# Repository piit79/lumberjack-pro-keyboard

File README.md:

# Lumberjack Pro - Hotswap ortholinear 60% keyboard PCB based on the Frood/nice!nano

Lumberjack is a hotswap split 5x12 ortholinear keyboard PCB based on the Frood or nice!nano controllers, and using mostly through-hole components.

The goal of this project is to build a hotswap ortholinear PCB that fits in many standard 60% tray mount cases.

Inspired by the [Plaid keyboard](https://github.com/hsgw/plaid).

* Designed to be easy to build with minimal soldering experience
* Uses either the modern [Frood](https://42keebs.eu/shop/parts/controllers/frood-rp2040-pro-micro-controller/) (wired) or [nice!nano](https://nicekeyboards.com/nice-nano) (wireless) controllers instead of the old-school 8bit ATmega MCU
* Uses Kailh hotswap sockets for easy switch swaps
* Get that visible component aesthetic in a standard 60% tray-mount case
* Supports both USB Mini and USB-C
* Plateless or with FR4 switch plates

# Kit availability

Complete kits can be purchased at [42. Keebs](https://42keebs.eu/shop/kits/pro-micro-based/lumberjack-pro-hotswap-50-ortho-kit/)

# Ordering parts

See the [Bill of materials](BOM.md) for a detailed list of the required parts.

PCBs can be manufactuered by a variety of online PCB fabricators. You can use [PCBShopper](https://pcbshopper.com/) to search for the best price.

The [zip file in the releases](https://github.com/piit79/lumberjack-pro-keyboard/releases) contains the gerber files your fabricator will need to make the PCB.

When uploading the gerber zip files, use the default PCB settings.

Note that when uploading to JLCPCB, the upload tool may not detect the dimensions of the PCB from the gerber files and may not generate a preview image. This appears to be an issue with JLCPCB and you can manually enter the PCB size as 94.6x285mm.

If you want to use a plate, there are gerbers for an FR4 plate. You will need two plates, one for each half of the keyboard.

# Construction

Solder all the components onto the top side of the PCB except the USB connector which should be on the back of the board. Leave the larger components until last so that the board will lie flat upsidedown while you solder the resistors and capacitors.

Ensure that the diodes are installed in the correct orientation. The square pad is for the side with the black stripe.

See [the build guide](guide.md) for more information.

## Need help?

Have questions or need help, reach out via the [42. Keebs Discord server](https://42keebs.eu/discord) where you will find many helpful Lumberjack owners.

# Firmware

Firmware is available in our [QMK/Vial fork](https://github.com/piit79/vial-qmk/tree/vial/keyboards/42keebs/lumberjack_pro).

Follow the [QMK firmware instructions](https://docs.qmk.fm/#/flashing) to build and flash the firmware.

To put the controller into bootloader mode so it is ready to recieve firmware, do the following:

* A brand new Frood and nice!nano will enter bootloader mode automatically
* On the Frood, hold the BOOT button while pressing the RESET button
* If the Frood is flashed with a QMK/Vial firmware, double-press the RESET button quickly
* On the nice!nano, double-press the RESET button quickly

Once the controller enters the bootloader mode, it will present itself as a USB mass storage device ("USB flash drive"). To flash the firmware .uf2 file, simply copy it to the drive.

# Component cover

Cut a piece of 2mm thick acrylic to size (95x57mm) and drill 4 m2 holes in the corners for the standoffs. Use the PCB or cover.dxf as a guide for the hole positions, you can also use cover.dxf for laser cutting the correct size acrylic.

Affix the 4 standoffs to the PCB with screws from underneath the PCB. Use the remaining 4 screws to attach the acrylic to the top of the standoffs.

# Revisions

## Rev1

* Initial revision using hotswap sockets with support for both Frood and nice!nano controllers

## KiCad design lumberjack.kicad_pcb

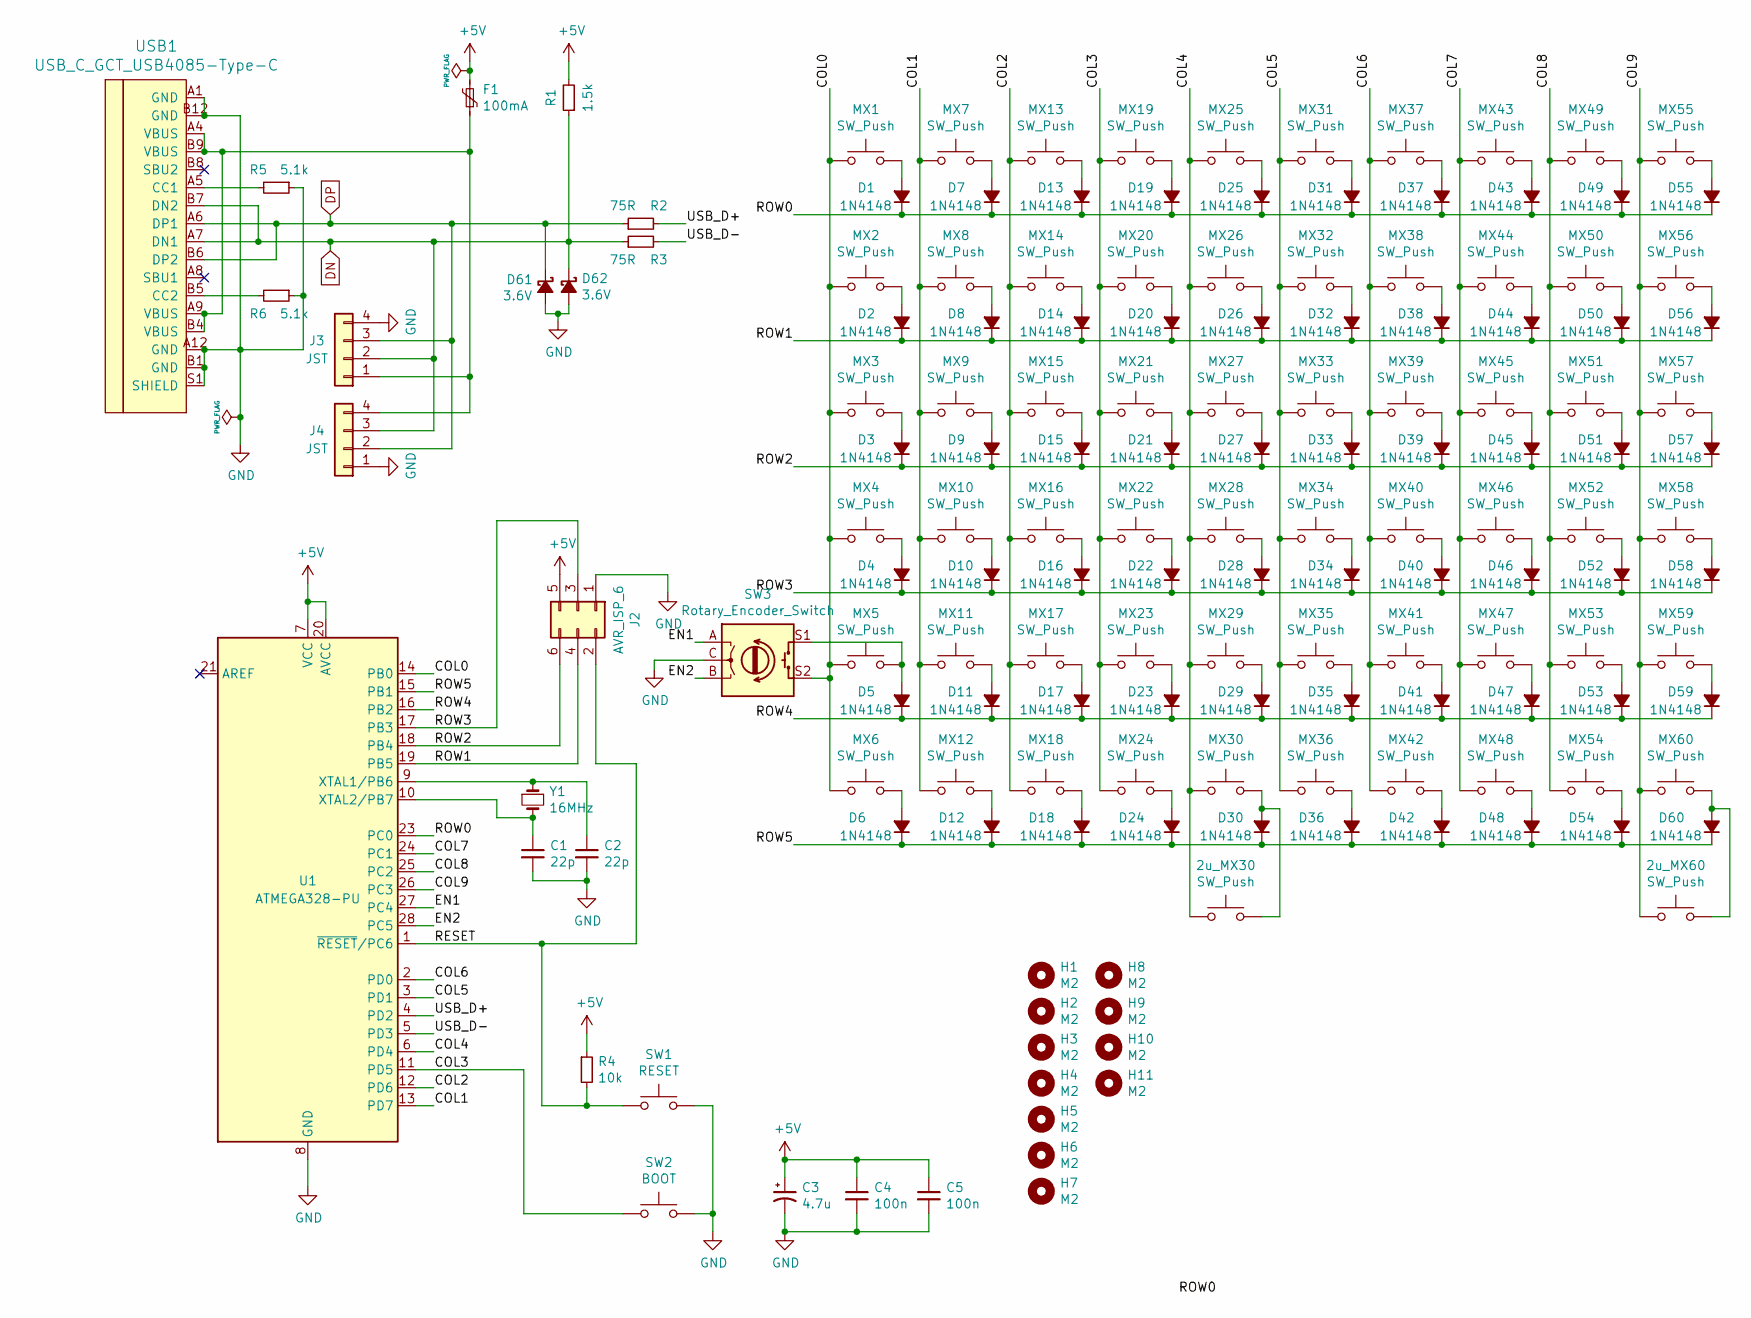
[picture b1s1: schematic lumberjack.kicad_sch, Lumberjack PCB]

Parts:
2u_MX30, 2u_MX60: SW_Push; MX_PCB_200B
C1, C2: 22p; C_Disc_D3.0mm_W1.6mm_P2.50mm
C3: 4.7u; CP_Radial_D4.0mm_P1.50mm
C4, C5: 100n; C_Disc_D4.3mm_W1.9mm_P5.00mm
D1, D2, D3, D4, D5, D6, D7, D8, D9, D10, D11, D12, D13, D14, D15, D16, D17, D18, D19, D20, D21, D22, D23, D24, D25, D26, D27, D28, D29, D30, D31, D32, D33, D34, D35, D36, D37, D38, D39, D40, D41, D42, D43, D44, D45, D46, D47, D48, D49, D50, D51, D52, D53, D54, D55, D56, D57, D58, D59, D60: 1N4148; D_DO-35_SOD27_P7.62mm_Horizontal
D61, D62: 3.6V; D_DO-35_SOD27_P7.62mm_Horizontal
F1: 100mA; Fuse_Bourns_MF-RHT100
H1, H2, H3, H4: M2; MountingHole_M2
H5, H6, H7: M2; MountingSlot_M2
H8, H9, H10, H11: M2; MountingHole_2.2mm_M2
J2: AVR_ISP_6; PinHeader_2x03_P2.54mm_Vertical
J3: JST; JST_SH_SM04B-SRSS-TB_1x04-1MP_P1.00mm_Horizontal
J4: JST; S4B-ZRLFSN
MX1, MX2, MX3, MX4, MX5, MX6, MX7, MX9, MX10, MX11, MX12, MX13, MX14, MX15, MX16, MX17, MX18, MX19, MX20, MX21, MX22, MX23, MX24, MX25, MX26, MX27, MX28, MX29, MX30, MX31, MX32, MX33, MX34, MX35, MX36, MX37, MX38, MX39, MX40, MX41, MX42, MX43, MX44, MX45, MX46, MX47, MX48, MX49, MX50, MX51, MX52, MX53, MX54, MX55, MX56, MX57, MX58, MX59, MX60: SW_Push; MX
MX8: SW_Push; MX_NTHSTH
R1: 1.5k; R_Axial_DIN0204_L3.6mm_D1.6mm_P7.62mm_Horizontal
R2, R3: 75R; R_Axial_DIN0204_L3.6mm_D1.6mm_P7.62mm_Horizontal
R4: 10k; R_Axial_DIN0204_L3.6mm_D1.6mm_P7.62mm_Horizontal
R5, R6: 5.1k; R_Axial_DIN0204_L3.6mm_D1.6mm_P7.62mm_Horizontal
SW1: RESET; SW_PUSH_6mm
SW2: BOOT; SW_PUSH_6mm
SW3: Rotary_Encoder_Switch; RotaryEncoder_Alps_EC11E-Switch_Vertical_H20mm-for-MX
U1: ATMEGA328-PU; DIP-28_W7.62mm
USB1: USB_C_GCT_USB4085-Type-C; USB_C_GCT_USB4085-offset-pads
Y1: 16MHz; Crystal_HC49-4H_Vertical

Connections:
+5V: C3.1, C4.1, C5.1, F1.2, J2.5, R1.2, R4.1, U1.7 (VCC), U1.20 (AVCC)
/COL0: MX1.2, MX2.2, MX3.2, MX4.2, MX5.2, MX6.2, SW3.S2, U1.14 (PB0)
/COL1: MX7.2, MX8.2, MX9.2, MX10.2, MX11.2, MX12.2, U1.13 (PD7)
/COL2: MX13.2, MX14.2, MX15.2, MX16.2, MX17.2, MX18.2, U1.12 (PD6)
/COL3: MX19.2, MX20.2, MX21.2, MX22.2, MX23.2, MX24.2, SW2.1, U1.11 (PD5)
/COL4: 2u_MX30.2, MX25.2, MX26.2, MX27.2, MX28.2, MX29.2, MX30.2, U1.6 (PD4)
/COL5: MX31.2, MX32.2, MX33.2, MX34.2, MX35.2, MX36.2, U1.3 (PD1)
/COL6: MX37.2, MX38.2, MX39.2, MX40.2, MX41.2, MX42.2, U1.2 (PD0)
/COL7: MX43.2, MX44.2, MX45.2, MX46.2, MX47.2, MX48.2, U1.24 (PC1)
/COL8: MX49.2, MX50.2, MX51.2, MX52.2, MX53.2, MX54.2, U1.25 (PC2)
/COL9: 2u_MX60.2, MX55.2, MX56.2, MX57.2, MX58.2, MX59.2, MX60.2, U1.26 (PC3)
/LED1: SW3.B, U1.28 (PC5); also elsewhere on the board
/LED2: SW3.A, U1.27 (PC4); also elsewhere on the board
/RESET: J2.2, R4.2, SW1.1, U1.1 (~RESET/PC6)
/ROW0: D1.1 (K), D7.1 (K), D13.1 (K), D19.1 (K), D25.1 (K), D31.1 (K), D37.1 (K), D43.1 (K), D49.1 (K), D55.1 (K), U1.23 (PC0)
/ROW1: D2.1 (K), D8.1 (K), D14.1 (K), D20.1 (K), D26.1 (K), D32.1 (K), D38.1 (K), D44.1 (K), D50.1 (K), D56.1 (K), J2.4, U1.19 (PB5)
/ROW2: D3.1 (K), D9.1 (K), D15.1 (K), D21.1 (K), D27.1 (K), D33.1 (K), D39.1 (K), D45.1 (K), D51.1 (K), D57.1 (K), J2.6, U1.18 (PB4)
/ROW3: D4.1 (K), D10.1 (K), D16.1 (K), D22.1 (K), D28.1 (K), D34.1 (K), D40.1 (K), D46.1 (K), D52.1 (K), D58.1 (K), J2.3, U1.17 (PB3)
/ROW4: D5.1 (K), D11.1 (K), D17.1 (K), D23.1 (K), D29.1 (K), D35.1 (K), D41.1 (K), D47.1 (K), D53.1 (K), D59.1 (K), U1.16 (PB2)
/ROW5: D6.1 (K), D12.1 (K), D18.1 (K), D24.1 (K), D30.1 (K), D36.1 (K), D42.1 (K), D48.1 (K), D54.1 (K), D60.1 (K), U1.15 (PB1)
/USB_D+: R2.2, U1.4 (PD2)
/USB_D-: R3.2, U1.5 (PD3)
GND: C1.2, C2.2, C3.2, C4.2, C5.2, D61.2 (A), D62.2 (A), J2.1, J3.4, J4.1, R5.1, R6.1, SW1.2, SW2.2, SW3.C, U1.8 (GND), U1.22 (GND), USB1.A1 (GND), USB1.A12 (GND), USB1.B1 (GND), USB1.B12 (GND), USB1.S1 (SHIELD); also elsewhere on the board
unnamed: 2u_MX30.1, D30.2 (A), MX30.1
unnamed: 2u_MX60.1, D60.2 (A), MX60.1
unnamed: C1.1, U1.10 (XTAL2/PB7), Y1.2
unnamed: C2.1, U1.9 (XTAL1/PB6), Y1.1
unnamed: D1.2 (A), MX1.1
unnamed: D2.2 (A), MX2.1
unnamed: D3.2 (A), MX3.1
unnamed: D4.2 (A), MX4.1
unnamed: D5.2 (A), MX5.1, SW3.S1
unnamed: D6.2 (A), MX6.1
unnamed: D7.2 (A), MX7.1
unnamed: D8.2 (A), MX8.1
unnamed: D9.2 (A), MX9.1
unnamed: D10.2 (A), MX10.1
unnamed: D11.2 (A), MX11.1
unnamed: D12.2 (A), MX12.1
unnamed: D13.2 (A), MX13.1
unnamed: D14.2 (A), MX14.1
unnamed: D15.2 (A), MX15.1
unnamed: D16.2 (A), MX16.1
unnamed: D17.2 (A), MX17.1
unnamed: D18.2 (A), MX18.1
unnamed: D19.2 (A), MX19.1
unnamed: D20.2 (A), MX20.1
unnamed: D21.2 (A), MX21.1
unnamed: D22.2 (A), MX22.1
unnamed: D23.2 (A), MX23.1
unnamed: D24.2 (A), MX24.1
unnamed: D25.2 (A), MX25.1
unnamed: D26.2 (A), MX26.1
unnamed: D27.2 (A), MX27.1
unnamed: D28.2 (A), MX28.1
unnamed: D29.2 (A), MX29.1
unnamed: D31.2 (A), MX31.1
unnamed: D32.2 (A), MX32.1
unnamed: D33.2 (A), MX33.1
unnamed: D34.2 (A), MX34.1
unnamed: D35.2 (A), MX35.1
unnamed: D36.2 (A), MX36.1
unnamed: D37.2 (A), MX37.1
unnamed: D38.2 (A), MX38.1
unnamed: D39.2 (A), MX39.1
unnamed: D40.2 (A), MX40.1
unnamed: D41.2 (A), MX41.1
unnamed: D42.2 (A), MX42.1
unnamed: D43.2 (A), MX43.1
unnamed: D44.2 (A), MX44.1
unnamed: D45.2 (A), MX45.1
unnamed: D46.2 (A), MX46.1
unnamed: D47.2 (A), MX47.1
unnamed: D48.2 (A), MX48.1
unnamed: D49.2 (A), MX49.1
unnamed: D50.2 (A), MX50.1
unnamed: D51.2 (A), MX51.1
unnamed: D52.2 (A), MX52.1
unnamed: D53.2 (A), MX53.1
unnamed: D54.2 (A), MX54.1
unnamed: D55.2 (A), MX55.1
unnamed: D56.2 (A), MX56.1
unnamed: D57.2 (A), MX57.1
unnamed: D58.2 (A), MX58.1
unnamed: D59.2 (A), MX59.1
unnamed: F1.1, J3.1, J4.4, USB1.A4 (VBUS), USB1.A9 (VBUS), USB1.B4 (VBUS), USB1.B9 (VBUS)
unnamed: R5.2, USB1.A5 (CC1)
unnamed: R6.2, USB1.B5 (CC2)

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
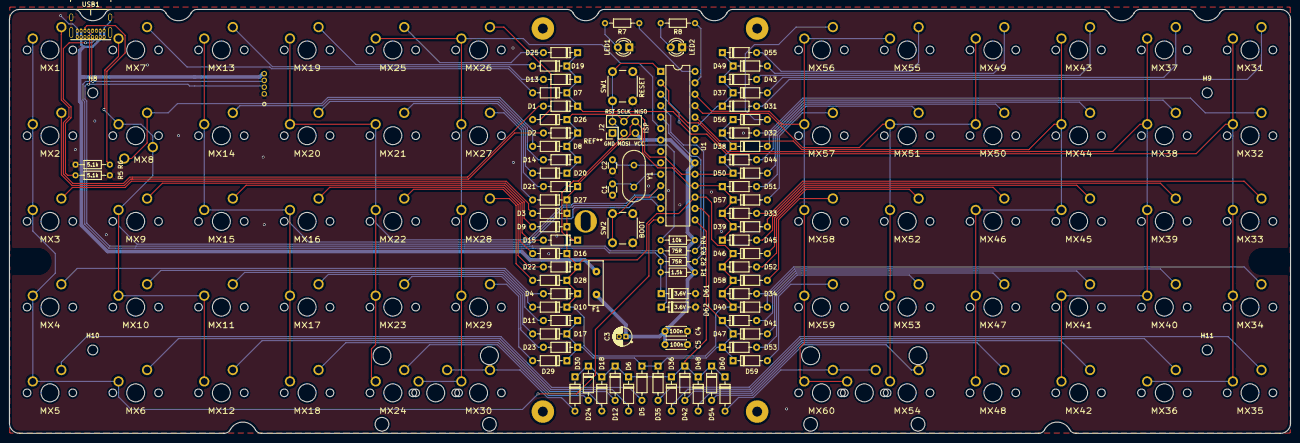
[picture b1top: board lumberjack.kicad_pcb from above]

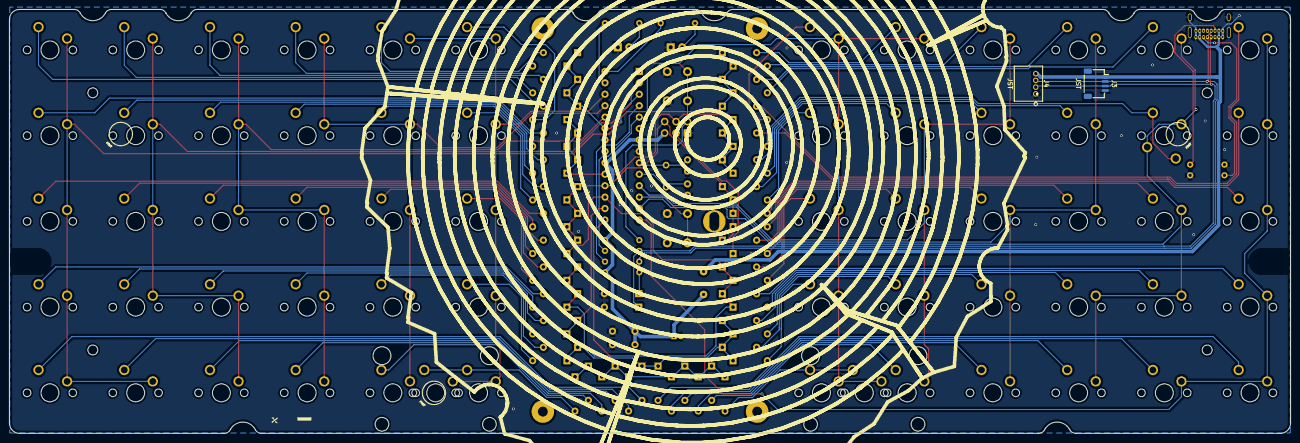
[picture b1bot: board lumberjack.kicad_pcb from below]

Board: 2 copper layers, 284.7 x 94.2 mm, 159 parts (2 on the bottom side), 92 nets.

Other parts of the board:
LED1: RED; LED_D3.0mm
LED2: GREEN; LED_D3.0mm
R7, R8: 1.5k; R_Axial_DIN0204_L3.6mm_D1.6mm_P7.62mm_Horizontal

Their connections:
/LED1: R7.1; also elsewhere on the board
/LED2: R8.1; also elsewhere on the board
GND: LED1.1, LED2.1; also elsewhere on the board
unnamed: LED1.2, R7.2
unnamed: LED2.2, R8.2

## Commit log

2021-11-26 Drop USB Mini, add mounting holes for case-less build
2022-02-01 Drop LEDs and add support for a rotary encoder instead (fixed)
    Switch to KiCad 6 project files
2022-02-01 Add PCB bottom plate + DXF
2022-02-01 Add modified plate gerbers with smaller side slot
2022-03-31 Switch to USB-C socket only for better alignment
    NB., gerber files have not been updated.
2022-03-31 Add support for an optional rotary encoder in the bottom left position
2022-03-31 Improve MX split plate: rounded corners, small slot
2022-11-10 WIP: PCB drawings, split plates
2023-02-01 Drop USB Mini support for better USB-C socket alignment
2023-02-01 Move decoupling caps close to the MCU
2023-02-02 Improve crystal ground loop to reduce RFI
2023-02-06 Add rotary encoder support; fix DRC errors
2023-02-06 Update gerber files
2023-07-12 Update the gerber zip and plate
2024-05-31 Rename project files to lumberjack-pro-frood
2024-05-31 Add lock files to .gitignore
2024-05-31 Add 42. Keebs KiCad library
2024-05-31 Remove {sym|fp}-lib-table/fp-info-cache files from gitignore
2024-05-31 Add {sym|fp}-lib-table/fp-info-cache to git
2024-05-31 WIP: replace discrete MCU with the Frood
2024-06-02 Update the 42. Keebs KiCad library
2024-09-04 Rename project to lumberjack-pro-keyboard
2024-09-04 Remove obsolete bootloader files
2024-11-17 Use smaller cover mounting holes
2024-11-17 Update README, BOM and guide

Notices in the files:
parts and their libraries:
Copyright 2021 Accelerated Designs. All rights reserved.
